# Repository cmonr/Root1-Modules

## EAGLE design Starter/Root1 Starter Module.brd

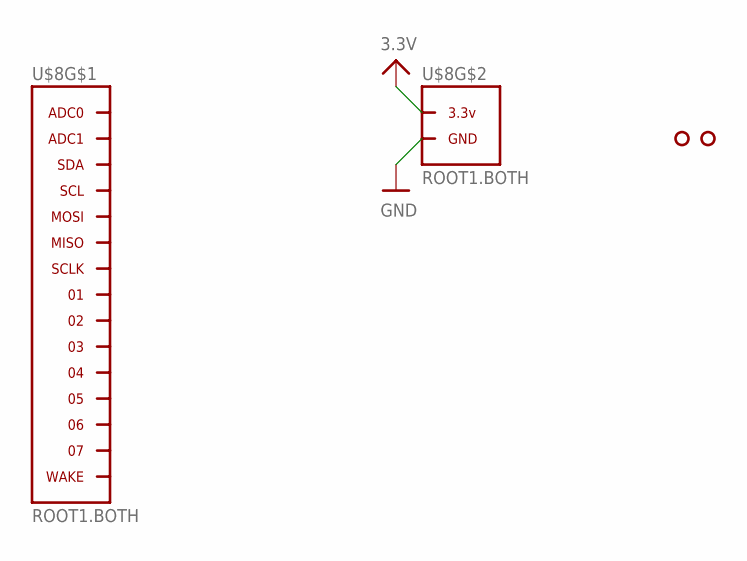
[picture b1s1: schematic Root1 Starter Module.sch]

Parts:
U$3, U$4: HOLE.2MM; 2MM
U$8: ROOT1.BOTH

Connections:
3.3V: U$8.3.3V@1 (3.3V), U$8.3.3V@2 (3.3V), U$8.3.3V@3 (3.3V), U$8.3.3V@4 (3.3V), U$8.3.3V@5 (3.3V), U$8.3.3V@6 (3.3V), U$8.3.3V@7 (3.3V), U$8.3.3V@8 (3.3V), U$8.3.3V@9 (3.3V), U$8.3.3V@10 (3.3V), U$8.3.3V@VIA (3.3V)
GND: U$8.GND@1 (GND), U$8.GND@2 (GND), U$8.GND@3 (GND), U$8.GND@4 (GND), U$8.GND@5 (GND), U$8.GND@6 (GND), U$8.GND@7 (GND), U$8.GND@8 (GND), U$8.GND@9 (GND), U$8.GND@10 (GND), U$8.GND@11 (GND), U$8.GND@12 (GND), U$8.GND@13 (GND), U$8.GND@14 (GND), U$8.GND@15 (GND), U$8.GND@16 (GND), U$8.GND@17 (GND), U$8.GND@18 (GND), U$8.GND@19 (GND), U$8.GND@20 (GND), U$8.GND@VIA (GND)
unnamed: U$8.ADC0, U$8.ADC0@1 (ADC0), U$8.ADC0@VIA (ADC0)
unnamed: U$8.ADC1, U$8.ADC1@1 (ADC1), U$8.ADC1@VIA (ADC1)
unnamed: U$8.SDA, U$8.SDA@1 (SDA), U$8.SDA@VIA (SDA)
unnamed: U$8.SCL, U$8.SCL@1 (SCL), U$8.SCL@VIA (SCL)
unnamed: U$8.MOSI, U$8.MOSI@1 (MOSI), U$8.MOSI@VIA (MOSI)
unnamed: U$8.MISO, U$8.MISO@1 (MISO), U$8.MISO@VIA (MISO)
unnamed: U$8.SCLK, U$8.SCLK@1 (SCLK), U$8.SCLK@VIA (SCLK)
unnamed: U$8.01, U$8.01@1 (01), U$8.01@VIA (01)
unnamed: U$8.02, U$8.02@1 (02), U$8.02@VIA (02)
unnamed: U$8.03, U$8.03@1 (03), U$8.03@VIA (03)
unnamed: U$8.04, U$8.04@1 (04), U$8.04@VIA (04)
unnamed: U$8.05, U$8.05@1 (05), U$8.05@VIA (05)
unnamed: U$8.06, U$8.06@1 (06), U$8.06@VIA (06)
unnamed: U$8.07, U$8.07@1 (07), U$8.07@VIA (07)
unnamed: U$8.WAKE, U$8.WAKE@1 (WAKE), U$8.WAKE@VIA (WAKE)

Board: 2 copper layers, 3 parts (0 on the bottom side), 17 nets, no tracks yet.

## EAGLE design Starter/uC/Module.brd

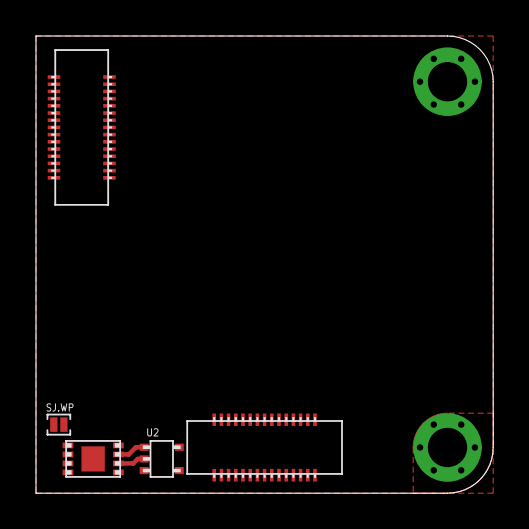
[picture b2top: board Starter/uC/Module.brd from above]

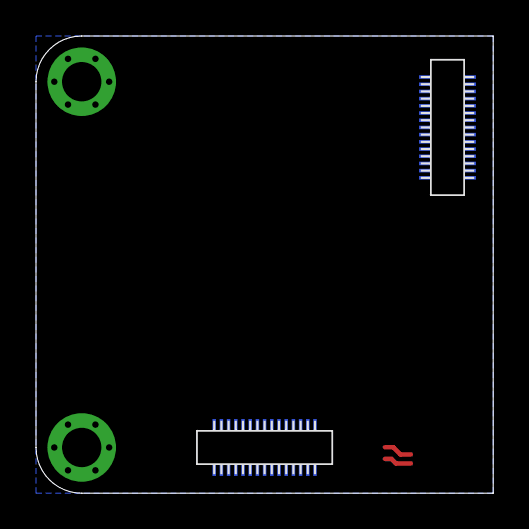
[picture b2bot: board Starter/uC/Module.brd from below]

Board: 2 copper layers, 25.4 x 25.4 mm, 7 parts (2 on the bottom side), 36 nets.

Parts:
J1, J2: DF40.30PIN.RECEPTACLE; DF40(XX)-30DS-0.4V
J3, J4: DF40.30PIN.HEADER; DF40(XX)-30DP-0.4V
SJ.WP: 2.MED
U1: CAT24CXX.UDFN; UDFN8.2X3MM
U2: NC7S86.SC70-5; SC70-5

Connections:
3.3V: J2.5, J4.1, J4.3, J4.5, J4.7, J4.9, J4.11, J4.13, J4.15, J4.17, J4.19, J4.21, J4.23, J4.25, U1.8, U2.6
A0: J2.3, J4.27, U1.1
A0.NEW: J2.1, J4.29, U2.4
A1: J2.4, J4.28, U1.2, U2.2
A2: J2.2, J4.30, U1.3, U2.1
ADC0: J1.2, J3.30
ADC1: J1.4, J3.28
GND: J1.3, J1.5, J1.7, J1.9, J1.11, J1.13, J1.15, J1.17, J1.19, J1.21, J1.23, J1.25, J1.27, J1.29, J3.1, J3.3, J3.5, J3.7, J3.9, J3.11, J3.13, J3.15, J3.17, J3.19, J3.21, J3.23, J3.25, J3.27, SJ.WP.2, U1.4, U1.PAD, U2.3
IO.0: J1.16, J3.16
IO.1: J1.18, J3.14
IO.2: J1.20, J3.12
IO.3: J1.22, J3.10
IO.4: J1.24, J3.8
IO.5: J1.26, J3.6
IO.6: J1.28, J3.4
IO.7: J1.30, J3.2
MISO: J1.12, J3.20
MOSI: J1.10, J3.22
unnamed: SJ.WP.1, U1.7
unnamed: J2.7, J2.9, J2.11, J2.13, J2.15, J2.17, J2.19, J2.21, J2.23, J2.25, J2.27, J2.29
N/C.0: J2.24, J4.8
N/C.1: J2.26, J4.6
N/C.2: J2.28, J4.4
N/C.3: J2.30, J4.2
RES.0: J2.14, J4.18
RES.1: J2.16, J4.16
RES.2: J2.18, J4.14
RES.3: J2.20, J4.12
RES.4: J2.22, J4.10
RXI: J1.8, J3.24
RXI.DBG: J2.12, J4.20
SCL: J2.8, J4.24, U1.6
SCLK: J1.14, J3.18
SDA: J2.6, J4.26, U1.5
TXO: J1.6, J3.26
TXO.DBG: J2.10, J4.22

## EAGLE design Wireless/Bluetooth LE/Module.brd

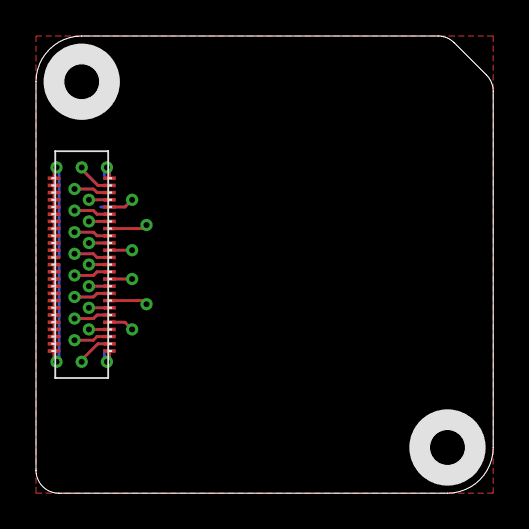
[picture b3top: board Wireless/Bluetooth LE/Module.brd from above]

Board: 2 copper layers, 25.4 x 25.4 mm, 3 parts (0 on the bottom side), 27 nets, no tracks yet.

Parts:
U$2: ROOT1.BOTH
U$3, U$4: HOLE.2MM; 2MM

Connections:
3.3V: U$2.3.3V@1, U$2.3.3V@2, U$2.3.3V@3, U$2.3.3V@4, U$2.3.3V@5, U$2.3.3V@6, U$2.3.3V@7, U$2.3.3V@8, U$2.3.3V@9, U$2.3.3V@10, U$2.3.3V@11, U$2.3.3V@12, U$2.3.3V@13, U$2.3.3V@14, U$2.3.3V@15, U$2.3.3V@16, U$2.3.3V@17, U$2.3.3V@18, U$2.3.3V@19, U$2.3.3V@20, U$2.3.3V@21, U$2.3.3V@22, U$2.3.3V@23, U$2.3.3V@24, U$2.3.3V@VIA
GND: U$2.GND@1, U$2.GND@2, U$2.GND@3, U$2.GND@4, U$2.GND@5, U$2.GND@6, U$2.GND@7, U$2.GND@8, U$2.GND@9, U$2.GND@10, U$2.GND@11, U$2.GND@12, U$2.GND@13, U$2.GND@14, U$2.GND@15, U$2.GND@16, U$2.GND@17, U$2.GND@18, U$2.GND@19, U$2.GND@20, U$2.GND@21, U$2.GND@22, U$2.GND@23, U$2.GND@24, U$2.GND@25, U$2.GND@26, U$2.GND@VIA
unnamed: U$2.04, U$2.04@1, U$2.04@VIA
unnamed: U$2.ADC1, U$2.ADC1@1, U$2.ADC1@VIA
unnamed: U$2.SDA, U$2.SDA@1, U$2.SDA@VIA
unnamed: U$2.SCL, U$2.SCL@1, U$2.SCL@VIA
unnamed: U$2.03, U$2.03@1, U$2.03@VIA
unnamed: U$2.MISO, U$2.MISO@1, U$2.MISO@VIA
unnamed: U$2.SCLK, U$2.SCLK@1, U$2.SCLK@VIA
unnamed: U$2.TXO, U$2.TXO@1, U$2.TXO@VIA
unnamed: U$2.RXI, U$2.RXI@1, U$2.RXI@VIA
unnamed: U$2.01, U$2.01@1, U$2.01@VIA
unnamed: U$2.02, U$2.02@1, U$2.02@VIA
unnamed: U$2.MOSI, U$2.MOSI@1, U$2.MOSI@VIA
unnamed: U$2.ADC0, U$2.ADC0@1, U$2.ADC0@VIA
unnamed: U$2.05, U$2.05@1, U$2.05@VIA
unnamed: U$2.06, U$2.06@1, U$2.06@VIA
unnamed: U$2.07, U$2.07@1, U$2.07@VIA
unnamed: U$2.WAKE, U$2.WAKE@1, U$2.WAKE@VIA
unnamed: U$2.TDI, U$2.TDI@1, U$2.TDI@VIA
unnamed: U$2.TDO, U$2.TDO@1, U$2.TDO@VIA
unnamed: U$2.TCK, U$2.TCK@1, U$2.TCK@VIA
unnamed: U$2.TMS, U$2.TMS@1, U$2.TMS@VIA
unnamed: U$2.TRST, U$2.TRST@1, U$2.TRST@VIA
unnamed: U$2.RXI.DBG, U$2.RXI.DBG@1, U$2.RXI.DBG@VIA
unnamed: U$2.TXO.DBG, U$2.TXO.DBG@1, U$2.TXO.DBG@VIA
unnamed: U$2.RST, U$2.RST@1, U$2.RST@VIA

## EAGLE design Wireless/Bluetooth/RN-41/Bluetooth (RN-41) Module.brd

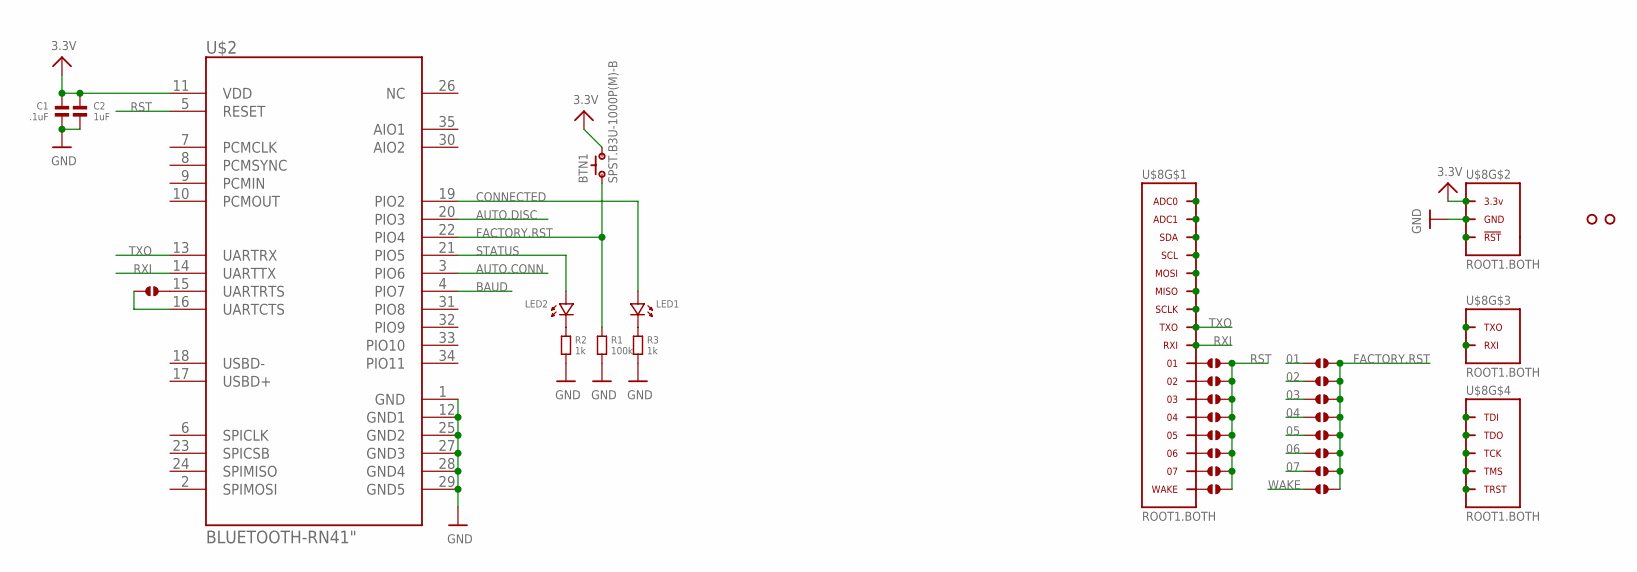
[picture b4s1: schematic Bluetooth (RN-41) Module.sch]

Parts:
01, 08: SOLDERJUMPER.2.SML; 2.SML
BTN1: SPST.B3U-1000P(M)-B; B3U-1000P(M)-B
C1: .1uF; 0603
C2: 1uF; 0603
J1: SOLDERJUMPER.2.LRG; 2.LRG
J2, J3, J4, J5, J6, J7, J8, J9, J10, J11, J12, J13, J14, J15: SOLDERJUMPER.2.SML; 2.SML
LED1, LED2: LED.0603; 0603.LED
R1: 100k; 0603
R2, R3: 1k; 0603
U$2: BLUETOOTH-RN41"; RN41
U$3, U$4: HOLE.2MM; 2MM
U$8: ROOT1.BOTH

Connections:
01: J2.1, J4.1, U$8.01, U$8.01@1 (01), U$8.01@VIA (01)
02: J3.1, J10.1, U$8.02, U$8.02@1 (02), U$8.02@VIA (02)
03: J5.1, J11.1, U$8.03, U$8.03@1 (03), U$8.03@VIA (03)
3.3V: BTN1.2, C1.1, C2.1, U$2.11 (VDD), U$8.3.3V@1 (3.3V), U$8.3.3V@2 (3.3V), U$8.3.3V@3 (3.3V), U$8.3.3V@4 (3.3V), U$8.3.3V@5 (3.3V), U$8.3.3V@6 (3.3V), U$8.3.3V@7 (3.3V), U$8.3.3V@8 (3.3V), U$8.3.3V@9 (3.3V), U$8.3.3V@10 (3.3V), U$8.3.3V@11 (3.3V), U$8.3.3V@12 (3.3V), U$8.3.3V@13 (3.3V), U$8.3.3V@14 (3.3V), U$8.3.3V@15 (3.3V), U$8.3.3V@16 (3.3V), U$8.3.3V@17 (3.3V), U$8.3.3V@18 (3.3V), U$8.3.3V@19 (3.3V), U$8.3.3V@20 (3.3V), U$8.3.3V@21 (3.3V), U$8.3.3V@22 (3.3V), U$8.3.3V@23 (3.3V), U$8.3.3V@24 (3.3V), U$8.3.3V@VIA (3.3V)
04: J6.1, J12.1, U$8.04, U$8.04@1 (04), U$8.04@VIA (04)
05: J7.1, J13.1, U$8.05, U$8.05@1 (05), U$8.05@VIA (05)
06: J8.1, J14.1, U$8.06, U$8.06@1 (06), U$8.06@VIA (06)
07: J9.1, J15.1, U$8.07, U$8.07@1 (07), U$8.07@VIA (07)
AUTO.CONN: U$2.3 (PIO6)
AUTO.DISC: U$2.20 (PIO3)
BAUD: U$2.4 (PIO7)
CONNECTED: LED1.P$1 (1), U$2.19 (PIO2)
FACTORY.RST: 01.2, BTN1.1, J4.2, J10.2, J11.2, J12.2, J13.2, J14.2, J15.2, R1.1, U$2.22 (PIO4)
GND: C1.2, C2.2, R1.2, R2.2, R3.2, U$2.1 (GND), U$2.12 (GND1), U$2.25 (GND2), U$2.27 (GND3), U$2.28 (GND4), U$2.29 (GND5), U$8.GND@1 (GND), U$8.GND@2 (GND), U$8.GND@3 (GND), U$8.GND@4 (GND), U$8.GND@5 (GND), U$8.GND@6 (GND), U$8.GND@7 (GND), U$8.GND@8 (GND), U$8.GND@9 (GND), U$8.GND@10 (GND), U$8.GND@11 (GND), U$8.GND@12 (GND), U$8.GND@13 (GND), U$8.GND@14 (GND), U$8.GND@15 (GND), U$8.GND@16 (GND), U$8.GND@17 (GND), U$8.GND@18 (GND), U$8.GND@19 (GND), U$8.GND@20 (GND), U$8.GND@21 (GND), U$8.GND@22 (GND), U$8.GND@23 (GND), U$8.GND@24 (GND), U$8.GND@25 (GND), U$8.GND@26 (GND), U$8.GND@VIA (GND)
unnamed: U$8.ADC0, U$8.ADC0@1 (ADC0), U$8.ADC0@VIA (ADC0)
unnamed: U$8.ADC1, U$8.ADC1@1 (ADC1), U$8.ADC1@VIA (ADC1)
unnamed: U$8.SDA, U$8.SDA@1 (SDA), U$8.SDA@VIA (SDA)
unnamed: U$8.SCL, U$8.SCL@1 (SCL), U$8.SCL@VIA (SCL)
unnamed: U$8.MOSI, U$8.MOSI@1 (MOSI), U$8.MOSI@VIA (MOSI)
unnamed: U$8.MISO, U$8.MISO@1 (MISO), U$8.MISO@VIA (MISO)
unnamed: U$8.SCLK, U$8.SCLK@1 (SCLK), U$8.SCLK@VIA (SCLK)
unnamed: J1.2, U$2.15 (UARTRTS)
unnamed: J1.1, U$2.16 (UARTCTS)
unnamed: LED2.P$2 (2), R2.1
unnamed: U$8.TRST, U$8.TRST@1 (TRST), U$8.TRST@VIA (TRST)
unnamed: U$8.TMS, U$8.TMS@1 (TMS), U$8.TMS@VIA (TMS)
unnamed: U$8.TCK, U$8.TCK@1 (TCK), U$8.TCK@VIA (TCK)
unnamed: U$8.TDO, U$8.TDO@1 (TDO), U$8.TDO@VIA (TDO)
unnamed: U$8.TDI, U$8.TDI@1 (TDI), U$8.TDI@VIA (TDI)
unnamed: U$8.RXI.DBG (RXI), U$8.RXI.DBG@1 (RXI), U$8.RXI.DBG@VIA (RXI)
unnamed: U$8.TXO.DBG (TXO), U$8.TXO.DBG@1 (TXO), U$8.TXO.DBG@VIA (TXO)
unnamed: U$8.RST (!RST), U$8.RST@1 (!RST), U$8.RST@VIA (!RST)
unnamed: LED1.P$2 (2), R3.1
RST: 08.2, J2.2, J3.2, J5.2, J6.2, J7.2, J8.2, J9.2, U$2.5 (RESET)
RXI: U$2.14 (UARTTX), U$8.RXI, U$8.RXI@1 (RXI), U$8.RXI@VIA (RXI)
STATUS: LED2.P$1 (1), U$2.21 (PIO5)
TXO: U$2.13 (UARTRX), U$8.TXO, U$8.TXO@1 (TXO), U$8.TXO@VIA (TXO)
WAKE: 01.1, 08.1, U$8.WAKE, U$8.WAKE@1 (WAKE), U$8.WAKE@VIA (WAKE)

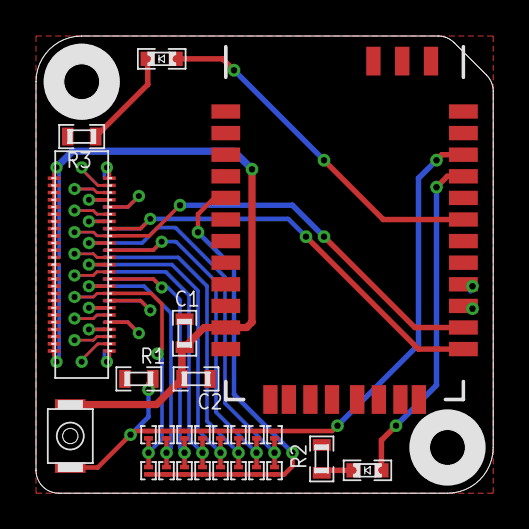
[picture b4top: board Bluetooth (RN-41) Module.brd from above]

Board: 2 copper layers, 25.4 x 25.4 mm, 29 parts (1 on the bottom side), 35 nets.

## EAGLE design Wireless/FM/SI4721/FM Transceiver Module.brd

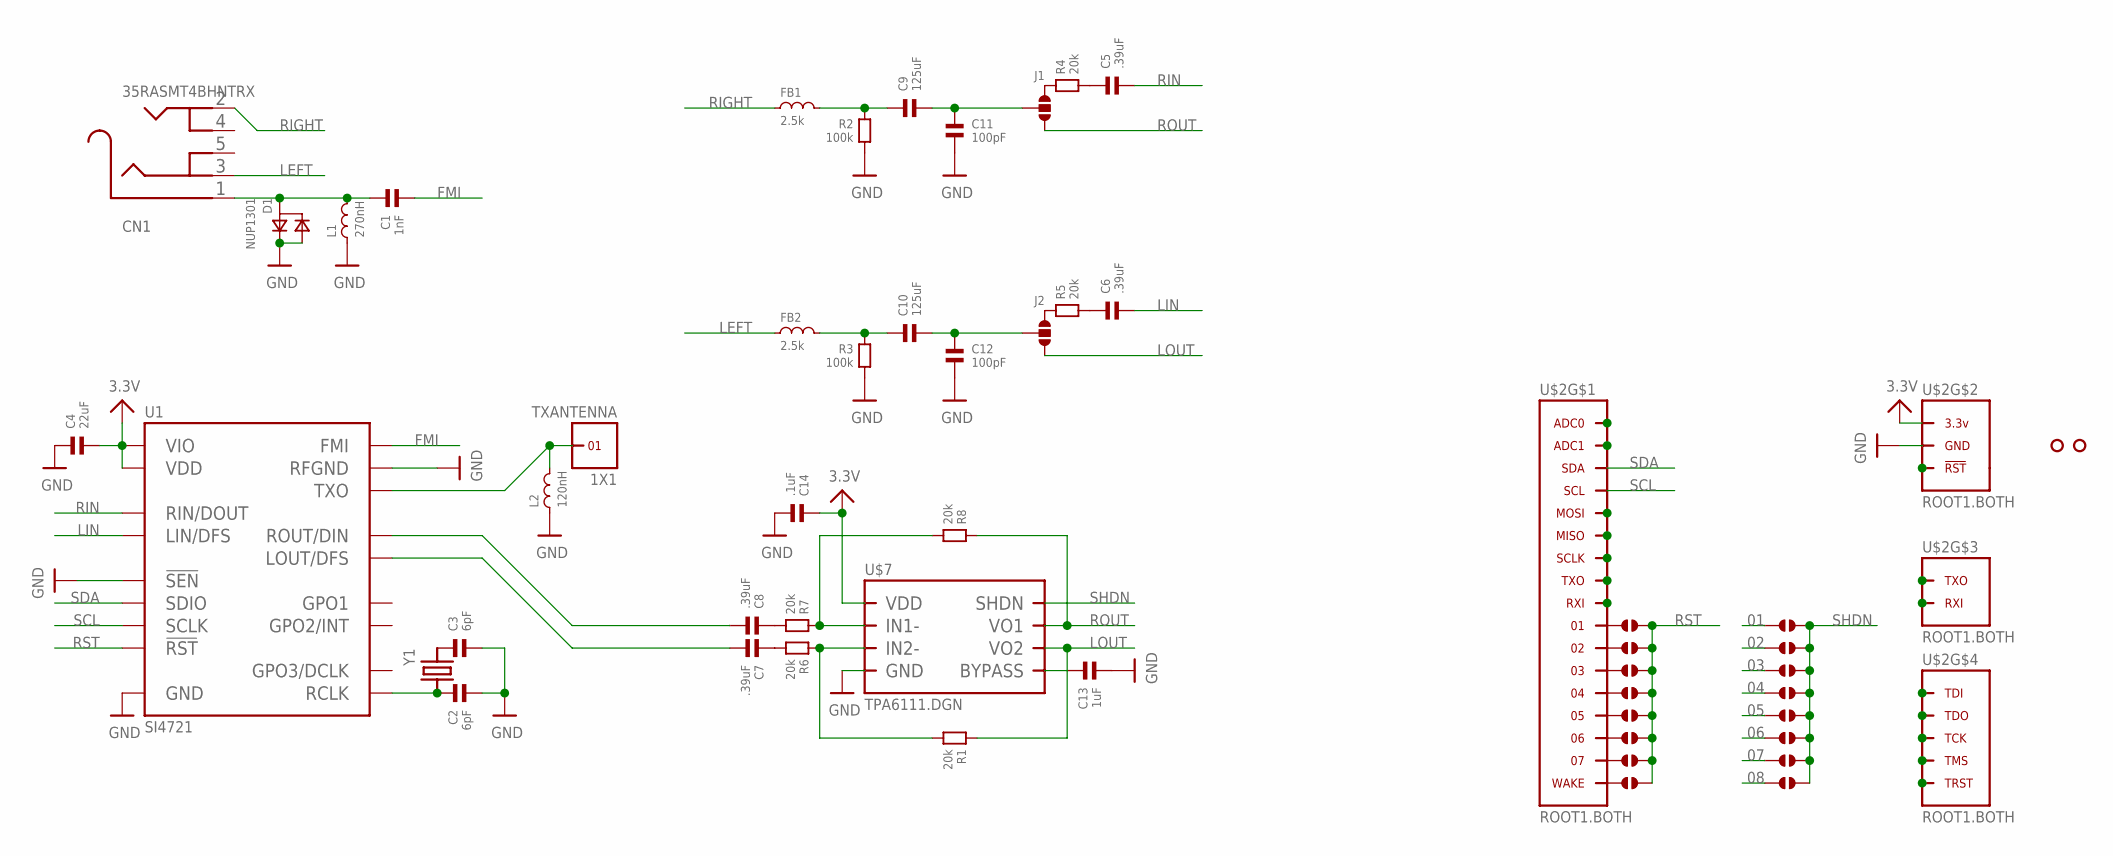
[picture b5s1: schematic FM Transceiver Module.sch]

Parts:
C1: 1nF; 0603
C2, C3: 6pF; 0603
C4: 22uF; 0805
C5, C6, C7, C8: .39uF; 0603
C9, C10: 125uF; 0603
C11, C12: 100pF; 0603
C13: 1uF; 0603
C14: .1uF; 0603
CN1: 35RASMT4BHNTRX; 4UCONN_19269
D1: NUP1301; SOT23
FB1, FB2: 2.5k; 0603
J1, J2: SOLDERJUMPER.3.LRG.12; 3.LRG.12
J3, J4, J5, J6, J7, J8, J9, J10, J11, J12, J13, J14, J15, J16, J17, J18: SOLDERJUMPER.2.SML; 2.SML
L1: 270nH; 0603
L2: 120nH; 0603
R1, R4, R5, R6, R7, R8: 20k; 0603
R2, R3: 100k; 0603
TXANTENNA: 1X1
U1: SI4721; QFN20
U$2: ROOT1.BOTH
U$3, U$4: HOLE.2MM; 2MM
U$7: TPA6111.DGN; DGN
Y1: CRYSTAL.ABS07; ABS07

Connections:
01: J3.1, J11.1, U$2.01, U$2.01@1 (01), U$2.01@VIA (01)
02: J4.1, J12.1, U$2.02, U$2.02@1 (02), U$2.02@VIA (02)
03: J5.1, J13.1, U$2.03, U$2.03@1 (03), U$2.03@VIA (03)
3.3V: C4.2, C14.1, U1.10 (VIO), U1.11 (VDD), U$2.3.3V@1 (3.3V), U$2.3.3V@2 (3.3V), U$2.3.3V@3 (3.3V), U$2.3.3V@4 (3.3V), U$2.3.3V@5 (3.3V), U$2.3.3V@6 (3.3V), U$2.3.3V@7 (3.3V), U$2.3.3V@8 (3.3V), U$2.3.3V@9 (3.3V), U$2.3.3V@10 (3.3V), U$2.3.3V@11 (3.3V), U$2.3.3V@12 (3.3V), U$2.3.3V@13 (3.3V), U$2.3.3V@14 (3.3V), U$2.3.3V@15 (3.3V), U$2.3.3V@16 (3.3V), U$2.3.3V@17 (3.3V), U$2.3.3V@18 (3.3V), U$2.3.3V@19 (3.3V), U$2.3.3V@20 (3.3V), U$2.3.3V@21 (3.3V), U$2.3.3V@22 (3.3V), U$2.3.3V@23 (3.3V), U$2.3.3V@24 (3.3V), U$2.3.3V@VIA (3.3V), U$7.8 (VDD)
04: J6.1, J14.1, U$2.04, U$2.04@1 (04), U$2.04@VIA (04)
05: J7.1, J15.1, U$2.05, U$2.05@1 (05), U$2.05@VIA (05)
06: J8.1, J16.1, U$2.06, U$2.06@1 (06), U$2.06@VIA (06)
07: J9.1, J17.1, U$2.07, U$2.07@1 (07), U$2.07@VIA (07)
08: J10.1, J18.1, U$2.WAKE, U$2.WAKE@1 (WAKE), U$2.WAKE@VIA (WAKE)
FMI: C1.2, U1.2 (FMI)
GND: C2.2, C3.2, C4.1, C11.2, C12.2, C13.2, C14.2, D1.1, D1.2, L1.1, L2.1, R2.2, R3.2, U1.3 (RFGND), U1.6 (!SEN), U1.12 (GND), U1.PAD (GND), U$2.GND@1 (GND), U$2.GND@2 (GND), U$2.GND@3 (GND), U$2.GND@4 (GND), U$2.GND@5 (GND), U$2.GND@6 (GND), U$2.GND@7 (GND), U$2.GND@8 (GND), U$2.GND@9 (GND), U$2.GND@10 (GND), U$2.GND@11 (GND), U$2.GND@12 (GND), U$2.GND@13 (GND), U$2.GND@14 (GND), U$2.GND@15 (GND), U$2.GND@16 (GND), U$2.GND@17 (GND), U$2.GND@18 (GND), U$2.GND@19 (GND), U$2.GND@20 (GND), U$2.GND@21 (GND), U$2.GND@22 (GND), U$2.GND@23 (GND), U$2.GND@24 (GND), U$2.GND@25 (GND), U$2.GND@26 (GND), U$2.GND@VIA (GND), U$7.4 (GND), U$7.PAD (GND)
LEFT: CN1.3, FB2.1
LIN: C6.2, U1.16 (LIN/DFS)
LOUT: J2.3, R1.1, U$7.7 (VO2)
LOUT.AMP: C7.2, U1.14 (LOUT/DFS)
unnamed: U$2.ADC1, U$2.ADC1@1 (ADC1), U$2.ADC1@VIA (ADC1)
unnamed: C13.1, U$7.3 (BYPASS)
unnamed: U$2.MISO, U$2.MISO@1 (MISO), U$2.MISO@VIA (MISO)
unnamed: U$2.SCLK, U$2.SCLK@1 (SCLK), U$2.SCLK@VIA (SCLK)
unnamed: U$2.TXO, U$2.TXO@1 (TXO), U$2.TXO@VIA (TXO)
unnamed: U$2.RXI, U$2.RXI@1 (RXI), U$2.RXI@VIA (RXI)
unnamed: U$2.MOSI, U$2.MOSI@1 (MOSI), U$2.MOSI@VIA (MOSI)
unnamed: U$2.ADC0, U$2.ADC0@1 (ADC0), U$2.ADC0@VIA (ADC0)
unnamed: U$2.TDI, U$2.TDI@1 (TDI), U$2.TDI@VIA (TDI)
unnamed: U$2.TDO, U$2.TDO@1 (TDO), U$2.TDO@VIA (TDO)
unnamed: U$2.TCK, U$2.TCK@1 (TCK), U$2.TCK@VIA (TCK)
unnamed: U$2.TMS, U$2.TMS@1 (TMS), U$2.TMS@VIA (TMS)
unnamed: U$2.TRST, U$2.TRST@1 (TRST), U$2.TRST@VIA (TRST)
unnamed: U$2.RXI.DBG (RXI), U$2.RXI.DBG@1 (RXI), U$2.RXI.DBG@VIA (RXI)
unnamed: U$2.TXO.DBG (TXO), U$2.TXO.DBG@1 (TXO), U$2.TXO.DBG@VIA (TXO)
unnamed: U$2.RST (!RST), U$2.RST@1 (!RST), U$2.RST@VIA (!RST)
unnamed: R7.1, R8.2, U$7.2 (IN1-)
unnamed: C1.1, CN1.1, D1.3, L1.2
unnamed: C2.1, U1.9 (RCLK), Y1.2
unnamed: C9.2, C11.1, J1.2
unnamed: C3.1, Y1.1
unnamed: C10.2, C12.1, J2.2
unnamed: C5.1, R4.2
unnamed: C8.1, R7.2
unnamed: C6.1, R5.2
unnamed: C7.1, R6.2
unnamed: C9.1, FB1.2, R2.1
unnamed: C10.1, FB2.2, R3.1
unnamed: R1.2, R6.1, U$7.6 (IN2-)
unnamed: J2.1, R5.1
unnamed: J1.1, R4.1
RIGHT: CN1.2, FB1.1
RIN: C5.2, U1.15 (RIN/DOUT)
ROUT: J1.3, R8.1, U$7.1 (VO1)
ROUT.AMP: C8.2, U1.13 (ROUT/DIN)
RST: J3.2, J4.2, J5.2, J6.2, J7.2, J8.2, J9.2, J10.2, U1.5 (!RST)
SCL: U1.7 (SCLK), U$2.SCL, U$2.SCL@1 (SCL), U$2.SCL@VIA (SCL)
SDA: U1.8 (SDIO), U$2.SDA, U$2.SDA@1 (SDA), U$2.SDA@VIA (SDA)
SHDN: J11.2, J12.2, J13.2, J14.2, J15.2, J16.2, J17.2, J18.2, U$7.5 (SHDN)
TXO: L2.2, TXANTENNA.1, U1.4 (TXO)

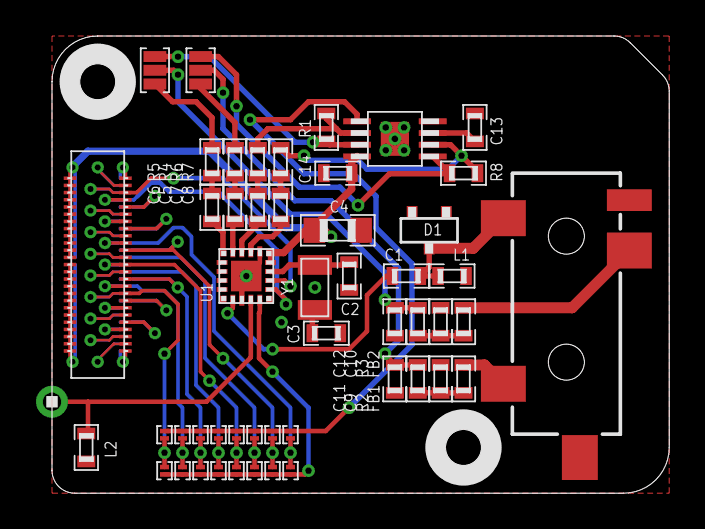
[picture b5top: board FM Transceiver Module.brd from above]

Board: 2 copper layers, 34.3 x 25.4 mm, 53 parts (0 on the bottom side), 55 nets.

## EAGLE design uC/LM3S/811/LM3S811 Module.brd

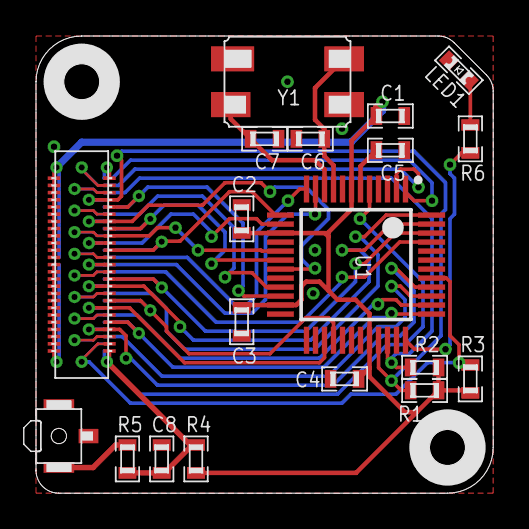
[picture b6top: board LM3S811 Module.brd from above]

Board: 2 copper layers, 25.4 x 25.4 mm, 21 parts (0 on the bottom side), 33 nets.

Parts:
C1, C2, C3, C4: .1uF; 0603
C5: 1uF; 0603
C6, C7: 18pF; 0603
C8: .01uF; 0603
LED1: 0603.LED
R1, R2: 2.2k; 0603
R3, R4: 10k; 0603
R5, R6: 470; 0603
U1: LM3S811; QFP50P900X900X160-48N
U$3, U$4: HOLE.2MM; 2MM
U$8: ROOT1.BOTH
U$10: B3U-3100P(M)-B
Y1: CRYSTAL.7X5MM; 7X5MM

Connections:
01: U1.14, U$8.01, U$8.01@1, U$8.01@VIA
02: U1.13, U$8.02, U$8.02@1, U$8.02@VIA
03: U1.12, U$8.03, U$8.03@1, U$8.03@VIA
3.3V: C1.1, C2.1, C3.1, C4.1, R1.1, R2.1, R3.1, R4.1, U1.7, U1.15, U1.23, U1.32, U$8.3.3V@1, U$8.3.3V@2, U$8.3.3V@3, U$8.3.3V@4, U$8.3.3V@5, U$8.3.3V@6, U$8.3.3V@7, U$8.3.3V@8, U$8.3.3V@9, U$8.3.3V@10, U$8.3.3V@11, U$8.3.3V@12, U$8.3.3V@13, U$8.3.3V@14, U$8.3.3V@15, U$8.3.3V@16, U$8.3.3V@17, U$8.3.3V@18, U$8.3.3V@19, U$8.3.3V@20, U$8.3.3V@21, U$8.3.3V@22, U$8.3.3V@23, U$8.3.3V@24, U$8.3.3V@VIA
04: U1.11, U$8.04, U$8.04@1, U$8.04@VIA
05: U1.45, U$8.05, U$8.05@1, U$8.05@VIA
06: U1.46, U$8.06, U$8.06@1, U$8.06@VIA
07: U1.47, U$8.07, U$8.07@1, U$8.07@VIA
!RST: C8.1, R4.2, R5.1, U1.5, U$8.RST, U$8.RST@1, U$8.RST@VIA
ADC0: U1.1, U$8.ADC0, U$8.ADC0@1, U$8.ADC0@VIA
ADC1: U1.2, U$8.ADC1, U$8.ADC1@1, U$8.ADC1@VIA
GND: C1.2, C2.2, C3.2, C4.2, C5.2, C6.2, C7.2, C8.2, LED1.P$2, U1.8, U1.16, U1.24, U1.31, U$8.GND@1, U$8.GND@2, U$8.GND@3, U$8.GND@4, U$8.GND@5, U$8.GND@6, U$8.GND@7, U$8.GND@8, U$8.GND@9, U$8.GND@10, U$8.GND@11, U$8.GND@12, U$8.GND@13, U$8.GND@14, U$8.GND@15, U$8.GND@16, U$8.GND@17, U$8.GND@18, U$8.GND@19, U$8.GND@20, U$8.GND@21, U$8.GND@22, U$8.GND@23, U$8.GND@24, U$8.GND@25, U$8.GND@26, U$8.GND@VIA, U$10.2
MISO: U1.21, U$8.MISO, U$8.MISO@1, U$8.MISO@VIA
MOSI: U1.22, U$8.MOSI, U$8.MOSI@1, U$8.MOSI@VIA
unnamed: R5.2, U$10.1
unnamed: LED1.P$1, R6.1
unnamed: C5.1, U1.6
unnamed: R6.2, U1.36
unnamed: C7.1, U1.10, Y1.3
unnamed: C6.1, U1.9, Y1.1
RXI: U1.17, U$8.RXI, U$8.RXI@1, U$8.RXI@VIA
RXI.DBG: U1.27, U$8.RXI.DBG, U$8.RXI.DBG@1, U$8.RXI.DBG@VIA
SCL: R1.2, U1.33, U$8.SCL, U$8.SCL@1, U$8.SCL@VIA
SCLK: U1.19, U$8.SCLK, U$8.SCLK@1, U$8.SCLK@VIA
SDA: R2.2, U1.34, U$8.SDA, U$8.SDA@1, U$8.SDA@VIA
TCK: U1.40, U$8.TCK, U$8.TCK@1, U$8.TCK@VIA
TDI: U1.38, U$8.TDI, U$8.TDI@1, U$8.TDI@VIA
TDO: U1.37, U$8.TDO, U$8.TDO@1, U$8.TDO@VIA
TMS: U1.39, U$8.TMS, U$8.TMS@1, U$8.TMS@VIA
TRST: R3.2, U1.41, U$8.TRST, U$8.TRST@1, U$8.TRST@VIA
TXO: U1.18, U$8.TXO, U$8.TXO@1, U$8.TXO@VIA
TXO.DBG: U1.28, U$8.TXO.DBG, U$8.TXO.DBG@1, U$8.TXO.DBG@VIA
WAKE: U1.48, U$8.WAKE, U$8.WAKE@1, U$8.WAKE@VIA

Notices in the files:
parts and their libraries:
SparkFun: Licensing: CC v3.0 Share-Alike You are welcome to use this library for commercial purposes.
